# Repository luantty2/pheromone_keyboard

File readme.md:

# Pheromone

* [Overview](#overview)
    * [Testimonials](#testimonials)
    * [Copyright](#copyright)
* [Keymap](#keymap)
    * [Via](#via)
* [How to use](#how-to-use)
    * [Using rotary encoder with lightroom](#using-rotary-encoder-with-lightroom)
    * [Using slider with FL Studio](#using-slider-with-FL-Studio)
    * [Layer switching hack](#layer-switching-hack)
* [Build setup](#build-setup)
    * [Hardware](#hardware)
        * [PCB](#pcb)
        * [BOM](#bom)
    * [Software](#software)
        * [Bootloader](#bootloader)
        * [Flashing firmware](#flashing-firmware)
        * [Customizing oled screen](#customizing-oled-screen)
        * [Enable midi slider](#enable-midi-slider)
        * [Sorting CTRL, WIN and ALT](#sorting-ctrl,-win-and-alt)
        * [Customizing email address marco](#customizing-email-address-marco)
* [Assembly](#assembly)
    * [Plate](#plate)
    * [Case](#case)
    * [Slider cap](#slider-cap)
* [Bugs and improvements](#bugs-and-improvements)
* [To do](#to-do)

# Overview

Pheromone is a 63-key keyboard supports slide potentiometer, rotary encoder and oled screen. The slide potentiometer outputs a midi signal which can be recognized by any software reads midi input, however the stability is still being tested. The rotary encoder also outputs midi signal when the keyboard is switched to 'Lightroom' dedicated layer, once you pressed an letter key the knob will output a midi cc signal with different parameter, which allows you use a knob to adjust up to 26 sliders in lightroom(with 'photographer' keymap, it's even 78), most importantly, the value will not jump or jitter, oppositely it moves relatively and smoothly. The oled screen will show you the last letter key you pressed, the caps lock state and the layer you're currently staying. 

The firmware is fully QMK, see [build environment setup](https://docs.qmk.fm/#/getting_started_build_tools) then the [make instructions](https://docs.qmk.fm/#/getting_started_make_guide) for more information.

Firmware built with QMK version "0.7.101-10-g3eb82e-dirty".

[More photos](https://imgur.com/a/TCALTwa)

 Keyboard Maintainer: [luantty2](https://github.com/luantty2)

Make example for this keyboard (after setting up your build environment):

```
 make pheromone:default
```

<!-- ## Testimonials

Cherry's build:

[Back to top](#pheromone) -->

# Copyright

This project has no license currently, please understand what [no license](https://choosealicense.com/no-permission/) is.

<!--  -->

Someone started GB without permission, please don't buy from these sellers.

# Keymap

## Dimension

## Base layer

## Function layer

~~The encoder in func layer has the abilitity to contol screen brightness, however it's only compatible with macos currently.~~

The keycode of encoder in func layer has been updated to KC_BRIGHTNESS_UP and KC_BRIGHTNESS_DOWN, now it works on both Windows and MacOS.

## Lightroom layer

## Via

An easy tool for setting custom keycodes. [Download](https://caniusevia.com/) the Via configurator first, open and click via->import keyboards/pheromone/keymaps/via/info.json, via will detect the keyboard automatically.

you need to flash pheromone_via.hex from precompiled firmware folder before playing with via.

[Back to top](#pheromone)

# How to use

## Using rotary encoder with lightroom

To enable midi input for lightroom, you first need to make sure [MIDI2LR](https://rsjaffe.github.io/MIDI2LR/) plugin installed on your computer, plug in keyboard and restart lightroom, you should see a configure page, in which you could combine the output of rotary encoder with lightroom command.

A short video explanation: [link](https://youtu.be/1BtyvG6ujGs)

Before you start you should switch the keyboard layer to 'LTRM' by pressing "Fn" key twice, note that the current layer you're staying is displayed on oled screen. 

The rotary encoder outputs values on CC1 by default, now if you rotate the encoder, the MIDI2LR page should appear a new row written MIDI command of 'CC1', if it doesn't, click 'Rescan MIDI devices' button below.

Now that our midi command isn't assigned to a lightroom command, to do that we simply click the row written in 'Unassigned', then it should appear a huge amount of command we could assign with, provided you have chosen 'Basic Tone -> Brightness', what it does is you're able to control 'brightness' by rotating encoder.

__It's important to right click on your command row, and select 'Binary offset' in the pop up window, and click 'apply to all'.__

The rotary encoder is able to handle up to 26 different sliders with default keymap, and 78 different sliders with photographer keymap. 

#### Default keymap

With default keymap, simply tap any letter key then rotate encoder, you should see a new row appear, assign it to any command you want, for example: press 'E' and assign command to 'Basic Tone -> Exposure'.

#### Photographer keymap

With photographer keymap, besides tap letter key once, you're also allowed to tap it twice or 3 times, it will give different cc numbers according to your tapping times, with which you can handle up to 78 cc numbers. The assignment is the same as default keymap.

#### Writer keymap

Writer keymap does not support using rotary encoder to output midi signals.

<!--  -->

## Using slider with FL Studio

Firstly, let's configure our keyboard as a midi input device in FL studio, go to options -> MIDI settings, click 'enable' button if 'pheromone' is shown here.

If you want to use slider to control the master volume in Fl Studio, right click on the master volume icon, and select 'link to controller', move the slider on your keyboard then they should be automatically bound together.

## Layer switching hack

Normally you can tap 'Fn' once to switch to next layer, with this keyboard you are allowed to tap 'Fn' twice quickly to instantly switch back to base layer, regardless of what layer you're staying. What's more, if you tap 'Fn' twice quickly in base layer, it will bring you back to the layer you previously stayed, it's helpful when you're concentrating on your work since layer switching doesn't bother you.

[Back to top](#pheromone)

# Build setup

## Hardware

### PCB

The gerber files is ready to be manufactured, send it to any manufacturer you trust to be good. 

### BOM

|Parts|Footprint|Quantity|
|:---|:---|:---|
|22pf capactior |0805|2|
|1uf capactior|0805|1|
|100nf capactior |0805|4|
|4.7uf capactior|0805|1|
|1N4148W diode|SOD-123|63|
|10K resistor |0805|2|
|22ohm resistor|0805|2|
|16Mhz Crystal |3225|1|
|button switch for reset |6mm*2.5mm|1|
|rotary encoder|EC11|1|
|Kailh hot swap socket||63|
|OLED screen|0.91' SSD1306|1|
|slide potentiometer  |See info below|1|
|ATmega32U4-AU |TQFP-44|1|
|USB micro |USB_Micro-B_Molex|1|
|key switch ||63|

The slide potentiometer I'm using here is bought from [taobao](https://detail.tmall.com/item.htm?id=605360822904&spm=a1z09.2.0.0.62ba2e8dWNJi1c&_u=110cp31q45a9), The same one could be found [here](https://www.aliexpress.com/item/32967375420.html?spm=a2g0o.productlist.0.0.f9286d5aOqbvSl&algo_pvid=f2208a9b-aa38-42ff-b372-a72e9cf80c1a&algo_expid=f2208a9b-aa38-42ff-b372-a72e9cf80c1a-1&btsid=0ab50f0815852140246381305e15e4&ws_ab_test=searchweb0_0,searchweb201602_,searchweb201603_), in theory any other B10K slide potentiometer should also work fine, just remember to modify the footprint in KiCad if your slide potentiometer comes with a different size.
<!--  -->

The proper handle length of rotary encoder would be 15mm, so that it's easier to find a suitable cap for it, otherwise it can be too high or to low.

<!--  -->

*The handle length refer to as the 'L' length*

[Back to top](#pheromone)

## Software

### Bootloader
The firmware uses qmk-dfu as its bootloader, once you've got MCU and other parts soldered, you need to set bootloader for your MCU, normally you will want a USBISP as ISP flasher, or a pro micro wired to ISP socket on your keyboard.

Here I'm using a teensy 2.0 flashed with [this](https://github.com/qmk/qmk_firmware/blob/master/util/teensy_2.0_ISP_B0.hex) firmware, to learn how to turn your teensy or pro micro into a ISP flasher and how to wire it to your keyboard, follow the [guide](https://beta.docs.qmk.fm/for-makers-and-modders/isp_flashing_guide).

Make sure you wired correctly, open up terminal and type:

```
ls /dev/tty.usb*
```

then it will show something like */dev/tty.usbmodem123456*

copy the result, run the command below:

```
avrdude -c avrisp -p m32u4 -P /dev/tty.usbmodem123456 -U flash:w:"pheromone_default_bootloader.hex":a -U lfuse:w:0x5E:m -U hfuse:w:0xD9:m -U efuse:w:0xC3:m -U lock:w:0x3F:m
```
#### For DFU bootloader
If your MCU has preinstalled a default bootloader, there's no need to install qmk-dfu, add a line in *rules.mk* 
```
BOOTLOADER = atmel-dfu
```
and recompile.

### Flashing firmware

Re-plug in your keyboard, open [QMK-toolbox](https://qmk.fm/toolbox/), then press reset button on the back of PCB, the qmk toolbox will show you if it's detected our keyboard, if it does, simply find "pheromone_default.hex" and hit "flash" in qmk toolbox.

Once you've got qmk working, simply hold down esc when connecting keyboard to computer instead of pressing reset button to enter usb bootloader.

### Customizing oled screen

<!--  -->

<!--  -->

The oled screen always showing an image, in addition, it also shows you multiple useful information:
* the capslock state
* the last letter key you pressed
* the layer you're currently staying
* the midi cc value of an letter key if you're staying in 'LTRM' layer.

the font file is located in *keyboards/pheromone/keymaps/default/glcdfont.c*

Upload this file onto [helixfonteditor](https://helixfonteditor.netlify.com/), and you're able to modify the font and sprites. Once you've got your work done, overwrite the original file and recompile.

### Enable midi slider

The slider feature is not enabled by default, to enable it, edit *config.h* and uncomment the code below:
```
#define POT_ENABLE
```

You're able to detect the ouput value from using midi software, I'm using MIDI Monitor in this case.

<!--  -->

**The feature is still being tested.**
### Sorting CTRL, WIN and ALT
You may want to change the order of "Ctrl, Alt and Win", pheromone gives you an easy way to do that. 

Find the MOD_SEQUENCE_CAW marco in *config.h*, where 'C' stands for 'Ctrl', 'A' stands for 'Alt', and 'W' stands for 'Win'.
```
#define MOD_SEQUENCE_CAW /*normally for macos users*/

/* 
#define MOD_SEQUENCE_CWA /*normally for windows users*/

/*other sequences*/
#define MOD_SEQUENCE_WAC
#define MOD_SEQUENCE_WCA
#define MOD_SEQUENCE_AWC
#define MOD_SEQUENCE_ACW
*/
```
By default it's set to MOD_SEQUENCE_CAW, which means it's an order for mac users, if you gonna change the order to 'Ctrl, Win, Alt', then comment '#define MOD_SEQUENCE_CAW' and uncomment '#define MOD_SEQUENCE_CWA' and recompile.

### Customizing email address marco

When holding **right shift** and hit number '2', it will print an email address on screen,~~you can modify the address by editing line 559 in *keymap.c*:~~

~~SEND_STRING("your_email_address@xxx.com");~~

replcace your email address in *config.h*:
```
#ifdef EMAIL_ENABLE
	#define EMAIL_ADDRESS "your_email_address@xxx.com"
#endif
```

When holding left shift and number 2, it gives a '@' as usual.

Certainly if you don't want this marco, remove
```
#define EMAIL_ENABLE
```
in *config.h*.

[Back to top](#pheromone)

# Assembly

## Plate

The plate file is ready to be manufactured, either carbon fiber or brass is fine.

There are 6 screw holes on plate and pcb, allow you insert M2*10mm screws to enhance the tightness between switch and pcb, yet they are optional.

## Case

The case file is for 3D printing, either PLA or resin should be fine. 

After sanding and painting it actually gives you great surface. If you find some uneven gaps on surface, woodfiller and primer will help you smooth them.

<!-- All screws for mounting holes are M2.5 size, but you can modify them up to the actual situation. -->
The mounting holes are compatible with insert threads with 3.5mm outter diameter, the size of threads could be M2 or M2.5, the depth would better be 3mm.

If you choose PLA then it's easy to heat insert threads, but if you choose to use resin, like me, then it's a little tricky, you may want to glue your inset nuts to  every hole, and sanding nuts when necessary.

The buttom plate is made of acrylic cut by laser with 2mm thickness.

## Slider cap

The cap of slider is also 3D printed. The post-processing is the same as case.

[Back to top](#pheromone)

# Bugs and improvements

[Back to top](#pheromone)

# To do

[Back to top](#pheromone)

USB improvments: USB-C connector, ESD protection, etc.

MCU: considering switching to STM32F303CCT6.

RGB matrix using is31fl3733.

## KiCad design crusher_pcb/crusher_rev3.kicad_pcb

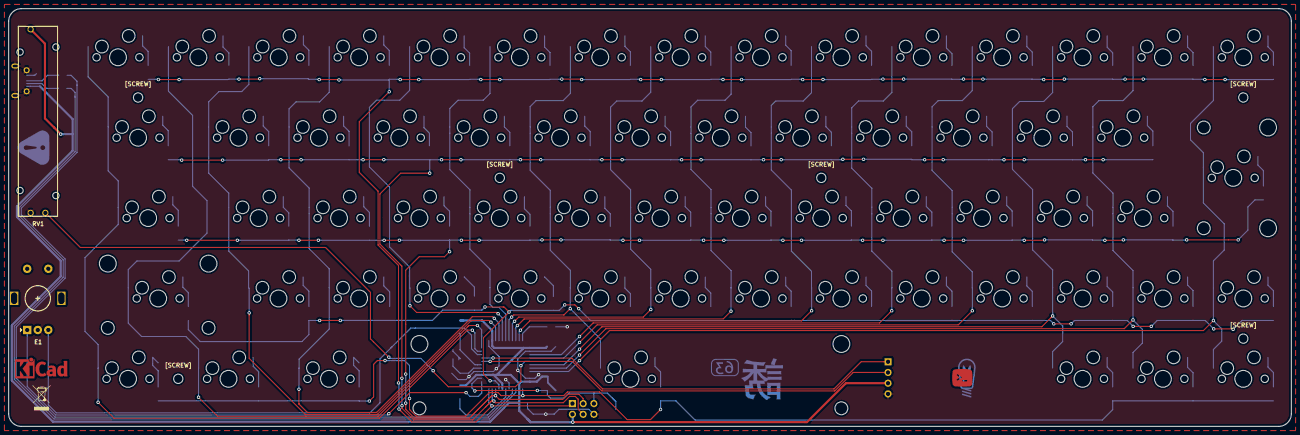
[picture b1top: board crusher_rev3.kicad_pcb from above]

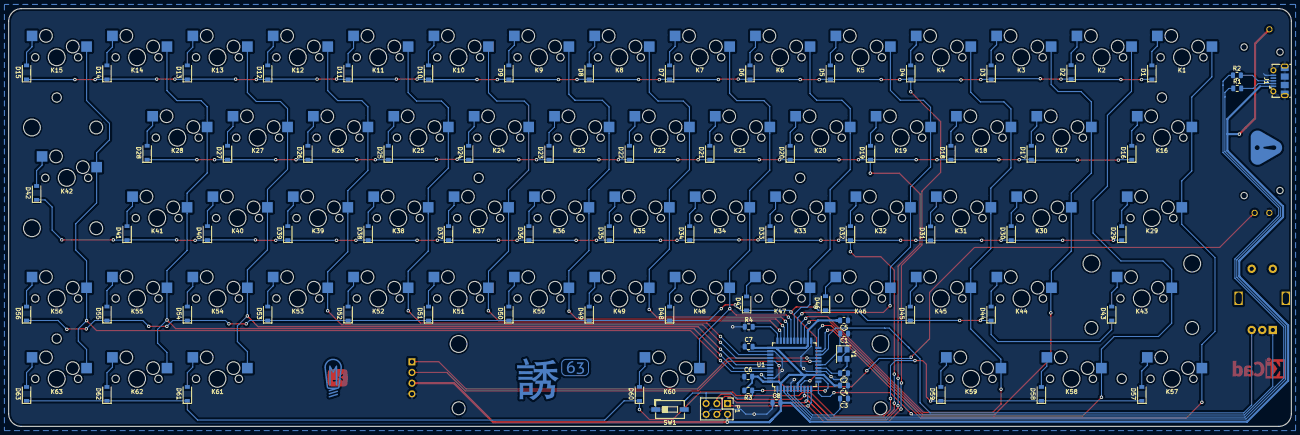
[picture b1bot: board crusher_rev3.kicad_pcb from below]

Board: 2 copper layers, 304.0 x 99.0 mm, 152 parts (80 on the bottom side), 99 nets.

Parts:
C1, C2: 22p; C_0805_2012Metric
C3: 1u; C_0805_2012Metric
C4, C5, C6, C7: 100n; C_0805_2012Metric
C8: 4.7u; C_0805_2012Metric
D1, D2, D3, D4, D5, D6, D7, D8, D9, D10, D11, D12, D13, D14, D15, D16, D17, D18, D19, D20, D21, D22, D23, D24, D25, D26, D27, D28, D29, D30, D31, D32, D33, D34, D35, D36, D37, D38, D39, D40, D41, D42, D43, D44, D45, D46, D47, D48, D49, D50, D51, D52, D53, D54, D55, D56, D57, D58, D59, D60, D61, D62, D63: D; D_SOD-123
E1: Rotary_Encoder_Switch; RotaryEncoder_Alps_EC11E-Switch_Vertical_H20mm
J1: USB_B_Micro; USB_Micro-B_Molex-105017-0001
K1, K2, K3, K4, K5, K6, K7, K8, K9, K10, K11, K12, K13, K14, K15, K17, K18, K19, K20, K21, K22, K23, K24, K25, K26, K27, K28, K30, K31, K32, K33, K34, K35, K36, K37, K38, K39, K40, K41, K44, K45, K46, K47, K48, K49, K50, K51, K52, K53, K54, K55, K56, K61, K62, K63: KEYSW; MXOnly-1U-Hotswap
K16: KEYSW; MXOnly-1.5U-Hotswap
K29: KEYSW; MXOnly-1.75U-Hotswap
K42: KEYSW; MXOnly-ISO-Hotswap
K43: KEYSW; MXOnly-2U-Hotswap-ReversedStabilizers
K57, K58, K59: KEYSW; MXOnly-1.25U-Hotswap
K60: KEYSW; MXOnly-6.25U-Hotswap-ReversedStabilizers
O1: Conn_01x04; 0.91_SSD1306_OLED
P1: AVR-ISP-6; PinHeader_2x03_P2.54mm_Vertical
R1, R2: 22; R_0805_2012Metric
R3, R4: 10k; R_0805_2012Metric
RV1: R_POT; potentiometer_slider_45mm
SW1: SW_PUSH; SW_DIP_SPSTx01_Slide_6.7x4.1mm_W6.73mm_P2.54mm_LowProfile_J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
U1: ATMEGA32U4; TQFP-44_10x10mm_Pitch0.8mm
Y1: Crystal_GND24; Crystal_SMD_3225-4Pin_3.2x2.5mm
[SCREW]: MountingHole_2.2mm_M2
[SCREW]#2, [SCREW]#3, [SCREW]#4, [SCREW]#5, [SCREW]#6: MountingHole_2.2mm_M2

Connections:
ANALOG: RV1.2, U1.38
COL0: K1.1, K16.1, K29.1, K57.1, U1.21
COL1: K2.1, K43.1, K58.1, U1.22
COL2: K3.1, K17.1, K30.1, K44.1, U1.25
COL3: K4.1, K18.1, K31.1, K45.1, K59.1, U1.26
COL4: K5.1, K19.1, K32.1, K46.1, U1.27
COL5: K6.1, K20.1, K33.1, K47.1, U1.28
COL6: K7.1, K21.1, K34.1, K48.1, K60.1, U1.29
COL7: K8.1, K22.1, K35.1, K49.1, U1.30
COL8: K9.1, K23.1, K36.1, K50.1, U1.31
COL9: K10.1, K24.1, K37.1, K51.1, U1.32
COL10: K11.1, K25.1, K38.1, K52.1, U1.36
COL11: K12.1, K26.1, K39.1, K53.1, U1.37
COL12: K13.1, K27.1, K40.1, K54.1, K61.1, U1.39
COL13: K14.1, K28.1, K41.1, K55.1, K62.1, U1.40
COL14: K15.1, K42.1, K56.1, K63.1, U1.41
GND: C1.1, C2.1, C3.1, C4.1, C5.1, C6.1, C7.1, C8.1, E1.C, J1.5, J1.6, O1.4, P1.6, R4.1, RV1.1, SW1.1, U1.5, U1.15, U1.23, U1.35, U1.43, Y1.2, Y1.4
MISO_ROW0: D1.1, D2.1, D3.1, D4.1, D5.1, D6.1, D7.1, D8.1, D9.1, D10.1, D11.1, D12.1, D13.1, D14.1, D15.1, P1.1, U1.11
MOSI_ROW1: D16.1, D17.1, D18.1, D19.1, D20.1, D21.1, D22.1, D23.1, D24.1, D25.1, D26.1, D27.1, D28.1, P1.4, U1.10
unnamed: C3.2, U1.6
unnamed: D1.2, K1.2
unnamed: D2.2, K2.2
unnamed: D3.2, K3.2
unnamed: D4.2, K4.2
unnamed: D5.2, K5.2
unnamed: D6.2, K6.2
unnamed: D7.2, K7.2
unnamed: D8.2, K8.2
unnamed: D9.2, K9.2
unnamed: D10.2, K10.2
unnamed: D11.2, K11.2
unnamed: D12.2, K12.2
unnamed: D13.2, K13.2
unnamed: D14.2, K14.2
unnamed: D15.2, K15.2
unnamed: D16.2, K16.2
unnamed: D17.2, K17.2
unnamed: D18.2, K18.2
unnamed: D19.2, K19.2
unnamed: D20.2, K20.2
unnamed: D21.2, K21.2
unnamed: D22.2, K22.2
unnamed: D23.2, K23.2
unnamed: D24.2, K24.2
unnamed: D25.2, K25.2
unnamed: D26.2, K26.2
unnamed: D27.2, K27.2
unnamed: D28.2, K28.2
unnamed: D29.2, K29.2
unnamed: D30.2, K30.2
unnamed: D31.2, K31.2
unnamed: D32.2, K32.2
unnamed: D33.2, K33.2
unnamed: D34.2, K34.2
unnamed: D35.2, K35.2
unnamed: D36.2, K36.2
unnamed: D37.2, K37.2
unnamed: D38.2, K38.2
unnamed: D39.2, K39.2
unnamed: D40.2, K40.2
unnamed: D41.2, K41.2
unnamed: D42.2, K42.2
unnamed: D43.2, K43.2
unnamed: D44.2, K44.2
unnamed: D45.2, K45.2
unnamed: D46.2, K46.2
unnamed: D47.2, K47.2
unnamed: D48.2, K48.2
unnamed: D49.2, K49.2
unnamed: D50.2, K50.2
unnamed: D51.2, K51.2
unnamed: D52.2, K52.2
unnamed: D53.2, K53.2
unnamed: D54.2, K54.2
unnamed: D55.2, K55.2
unnamed: D56.2, K56.2
unnamed: D57.2, K57.2
unnamed: D58.2, K58.2
unnamed: D59.2, K59.2
unnamed: D60.2, K60.2
unnamed: D61.2, K61.2
unnamed: D62.2, K62.2
unnamed: D63.2, K63.2
unnamed: J1.2, R1.2
unnamed: J1.3, R2.2
unnamed: R1.1, U1.3
unnamed: R2.1, U1.4
unnamed: R4.2, U1.33
ROW3: D43.1, D44.1, D45.1, D46.1, D47.1, D48.1, D49.1, D50.1, D51.1, D52.1, D53.1, D54.1, D55.1, D56.1, U1.8
ROW4: D57.1, D58.1, D59.1, D60.1, D61.1, D62.1, D63.1, U1.1
RST: P1.5, R3.1, SW1.2, U1.13
S0: E1.A, U1.12
S1: E1.B, U1.20
SCK_ROW2: D29.1, D30.1, D31.1, D32.1, D33.1, D34.1, D35.1, D36.1, D37.1, D38.1, D39.1, D40.1, D41.1, D42.1, P1.3, U1.9
SCL: O1.2, U1.18
SDA: O1.1, U1.19
VCC: C4.2, C5.2, C6.2, C7.2, C8.2, J1.1, O1.3, P1.2, R3.2, RV1.3, U1.2, U1.7, U1.14, U1.24, U1.34, U1.44
XTAL1: C2.2, U1.16, Y1.3
XTAL2: C1.2, U1.17, Y1.1

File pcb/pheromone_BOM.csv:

Comment,Description,Designator,Footprint,LibRef,Pins,Quantity,±àºÅ
LOGO,Desc,"G***,",monitor,LibRef,0,1
KiCad-Logo_5mm_Copper,Desc,"REF**,",KiCad-Logo_5mm_Copper,LibRef,0,1
WEEE-Logo_4.2x6mm_SilkScreen,Desc,"REF**,",WEEE-Logo_4.2x6mm_SilkScreen,LibRef,0,1
22p,Desc,"C2,C1,",C_0805_2012Metric,LibRef,2,2
1u,Desc,"C3,",C_0805_2012Metric,LibRef,2,1
100n,Desc,"C7,C6,C5,C4,",C_0805_2012Metric,LibRef,2,4
4.7u,Desc,"C8,",C_0805_2012Metric,LibRef,2,1
D,Desc,"D1,D2,D3,D4,D5,D6,D7,D8,D9,D10,D11,D12,D13,D14,D15,D16,D17,D18,D19,D20,D21,D22,D23,D24,D25,D26,D27,D28,D29,D30,D31,D32,D33,D34,D35,D36,D37,D38,D39,D40,D41,D42,D43,D44,D45,D46,D47,D48,D49,D50,D51,D52,D53,D54,D55,D56,D57,D58,D59,D60,D61,D62,D63,",D_SOD-123,LibRef,2,63
LOGO,Desc,"G***,",warning,LibRef,0,1
LOGO,Desc,"G***,",brand,LibRef,0,1
LOGO,Desc,"G***,",bulb,LibRef,0,1
22,Desc,"R2,R1,",R_0805_2012Metric,LibRef,2,2
10k,Desc,"R4,R3,",R_0805_2012Metric,LibRef,2,2
SW_PUSH,Desc,"SW1,",SW_DIP_SPSTx01_Slide_6.7x4.1mm_W6.73mm_P2.54mm_LowProfile_JPin,LibRef,2,1
ATMEGA32U4,Desc,"U1,",TQFP-44_10x10mm_Pitch0.8mm,LibRef,44,1
Crystal_GND24,Desc,"Y1,",Crystal_SMD_3225-4Pin_3.2x2.5mm,LibRef,4,1
Through Hole Items 
Rotary_Encoder_Switch,Desc,"E1,",RotaryEncoder_Alps_EC11E-Switch_Vertical_H20mm,LibRef,7,1
KEYSW,Desc,"K13,K56,K1,K2,K3,K4,K5,K6,K7,K8,K9,K10,K11,K12,K14,K15,K17,K18,K19,K20,K21,K22,K23,K24,K25,K26,K27,K28,K30,K31,K32,K33,K34,K35,K36,K37,K38,K39,K40,K41,K44,K45,K46,K47,K48,K49,K50,K51,K52,K53,K54,K55,K61,K62,K63,",MXOnly-1U-Hotswap,LibRef,7,55
KEYSW,Desc,"K16,",MXOnly-1.5U-Hotswap,LibRef,7,1
KEYSW,Desc,"K29,",MXOnly-1.75U-Hotswap,LibRef,7,1
KEYSW,Desc,"K42,",MXOnly-ISO-Hotswap,LibRef,11,1
KEYSW,Desc,"K43,",MXOnly-2U-Hotswap-ReversedStabilizers,LibRef,11,1
KEYSW,Desc,"K59,K58,K57,",MXOnly-1.25U-Hotswap,LibRef,7,3
KEYSW,Desc,"K60,",MXOnly-6.25U-Hotswap-ReversedStabilizers,LibRef,11,1
Conn_01x04,Desc,"O1,",0.91_SSD1306_OLED,LibRef,4,1
R_POT,Desc,"RV1,",potentiometer_slider_45mm,LibRef,7,1
MountingHole_2.2mm_M2,Desc,"[SCREW],[SCREW],[SCREW],[SCREW],[SCREW],[SCREW],",MountingHole_2.2mm_M2,LibRef,1,6
USB_B_Micro,Desc,"J1,",USB_Micro-B_Molex-105017-0001,LibRef,13,1
AVR-ISP-6,Desc,"P1,",PinHeader_2x03_P2.54mm_Vertical,LibRef,6,1

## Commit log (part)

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2020-02-18 INIT
2020-03-15 v0.01
2020-03-16 add tap dance for layer switching
2020-03-17 add precompiled firmware
2020-03-18 define for email address
2020-03-18 Revert "define for email address"
    This reverts commit 4b069514f8649718bfa99688ac937d42d7a30f10.
2020-03-18 add "define" for email macro
2020-03-18 update precompiled firmware
2020-03-18 add sorting mod keys feature
2020-03-19 add precompiled firmware for writer and photographer
2020-03-28 Enlarged mounting holes
2020-07-20 add via keymap
2020-07-20 add via precompiled firmware
2020-07-20 Add via support
2020-07-20 Update via support
2020-07-20 Add to do list
